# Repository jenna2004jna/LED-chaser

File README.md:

## Project Overview
Design an LED Chaser circuit (555 Timer + 4017 Decade Counter) and document the process for PCB fabrication using KiCad.

---

### 1. README (Project Introduction)

- **What is this?**
  An LED Chaser (aka LED Sequencer) using an NE555 Timer and CD4017 Decade Counter IC. This project demonstrates classic digital IC sequencing without microcontrollers.
- **Features:**
  - Chaser effect using 10 LEDs
  - Simple circuit, good for learning PCB design
  - Step-by-step development in KiCad
- **Repository Structure:**
  - `schematic/`   – KiCad schematic files
  - `pcb/`        – PCB layout files (KiCad)
  - `gerbers/`    – Generated manufacturing files
  - `docs/`       – Project documentation / images

---

### 2. Design Notes

- **Circuit Choice:**
  - 555 Timer (Astable mode) generates clock pulses
  - 4017 Decade Counter increments output, driving LEDs
- **Key Components:**
  - NE555 Timer IC
  - CD4017 Decade Counter IC
  - 10 LEDs (5mm, THT)
  - 10 Current limiting resistors (220Ω–330Ω)
  - Power: 5V or 9V
  - Decoupling capacitors (0.1µF at each IC's VCC/GND)
- **PCB Best Practices:**
  - Place ICs centrally
  - LED row for clear chaser effect
  - Power input near edge
  - Capacitors close to ICs
  - Use ground plane (GND zone) for noise immunity
  - Short 555-to-4017 clock trace
- **Fabrication:**
  - Run DRC in KiCad before generating Gerbers
  - Export Gerber and drill files for manufacturing (JLCPCB/PCBWay)

---

### 3. Bill of Materials (BOM)

| Qty | Reference           | Value         | Part Type   | Note                  |
|-----|---------------------|--------------|-------------|-----------------------|
| 1   | U1                  | NE555        | DIP-8       | Timer IC              |
| 1   | U2                  | CD4017       | DIP-16      | Decade Counter IC     |
| 10  | LED1–LED10          | 5mm          | THT         | Indicator LEDs        |
| 10  | R1–R10              | 220Ω–330Ω    | Axial       | LED current limiting  |
| 1   | R11                 | 10kΩ (ex)    | Axial       | 555 timing resistor   |
| 1   | C1                  | 10µF         | Radial      | 555 timing capacitor  |
| 2   | C2, C3              | 0.1µF        | Ceramic     | Decoupling capacitors |
| 1   | Conn1               | Power Input  | Header 2-pin| 5V or 9V supply       |

> Update ref/value as per your specific schematic.

---

### 4. Assembly & Testing Notes

- Solder components in order: resistors → IC sockets → LEDs → capacitors → power connector
- Double-check orientation of ICs and LEDs
- After assembly, power up and confirm LED chaser sequence
- If sequence fails, check clock trace length, decoupling cap placement, and solder joints

### 5. References & Further Reading

- [KiCad Official Documentation](https://docs.kicad.org/)
- [555 Timer & CD4017 datasheets](https://www.ti.com)
- [Example LED Chaser Circuits](https://www.electronics-tutorials.ws/sequential/seq_2.html)

---

**Maintainer:** jenna2004jna

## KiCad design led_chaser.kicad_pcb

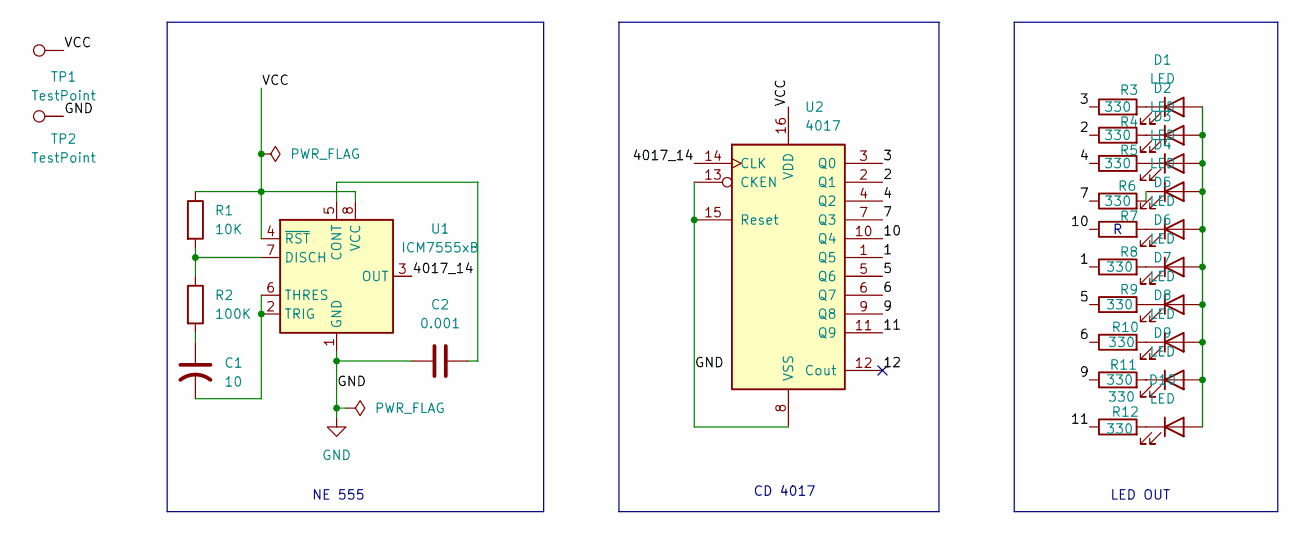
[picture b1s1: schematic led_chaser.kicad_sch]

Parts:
C1: 10; C_0805_2012Metric_Pad1.18x1.45mm_HandSolder
C2: 0.001; C_0805_2012Metric_Pad1.18x1.45mm_HandSolder
D1, D2, D3, D4, D5, D6, D7, D8, D9, D10: LED; LED_D5.0mm
R1: 10K; R_1206_3216Metric_Pad1.30x1.75mm_HandSolder
R2: 100K; R_1206_3216Metric_Pad1.30x1.75mm_HandSolder
R3, R4, R5, R6, R7, R8, R9, R10, R11, R12: 330; R_1206_3216Metric_Pad1.30x1.75mm_HandSolder
TP1, TP2: TestPoint; PinHeader_1x01_P2.54mm_Vertical
U1: ICM7555xB; SOIC-8_3.9x4.9mm_P1.27mm
U2: 4017; DIP-16_W7.62mm

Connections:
/1: R8.1, U2.1 (Q5)
/2: R4.1, U2.2 (Q1)
/3: R3.1, U2.3 (Q0)
/4: R5.1, U2.4 (Q2)
/5: R9.1, U2.5 (Q6)
/6: R10.1, U2.6 (Q7)
/7: R6.1, U2.7 (Q3)
/9: R11.1, U2.9 (Q8)
/10: R7.1, U2.10 (Q4)
/11: R12.1, U2.11 (Q9)
/12: U2.12 (Cout)
/4017_14: U1.3 (OUT), U2.14 (CLK)
/VCC: R1.1, TP1.1, U1.4 (~RST), U1.8 (VCC), U2.16 (VDD)
GND: C2.2, TP2.1, U1.1 (GND), U2.8 (VSS), U2.13 (CKEN), U2.15 (Reset)
unnamed: C1.1, R2.2
unnamed: D1.2 (A), D2.2 (A), D3.2 (A), D4.2 (A), D5.2 (A), D6.2 (A), D7.2 (A), D8.2 (A), D9.2 (A), D10.2 (A)
unnamed: D1.1 (K), R3.2
unnamed: D2.1 (K), R4.2
unnamed: D3.1 (K), R5.2
unnamed: D4.1 (K), R6.2
unnamed: D5.1 (K), R7.2
unnamed: D6.1 (K), R8.2
unnamed: D7.1 (K), R9.2
unnamed: D8.1 (K), R10.2
unnamed: D9.1 (K), R11.2
unnamed: D10.1 (K), R12.2
unnamed: C2.1, U1.5 (CONT)
unnamed: R1.2, R2.1, U1.7 (DISCH)
unnamed: C1.2, U1.2 (TRIG), U1.6 (THRES)

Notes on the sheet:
LED OUT
NE 555
CD 4017

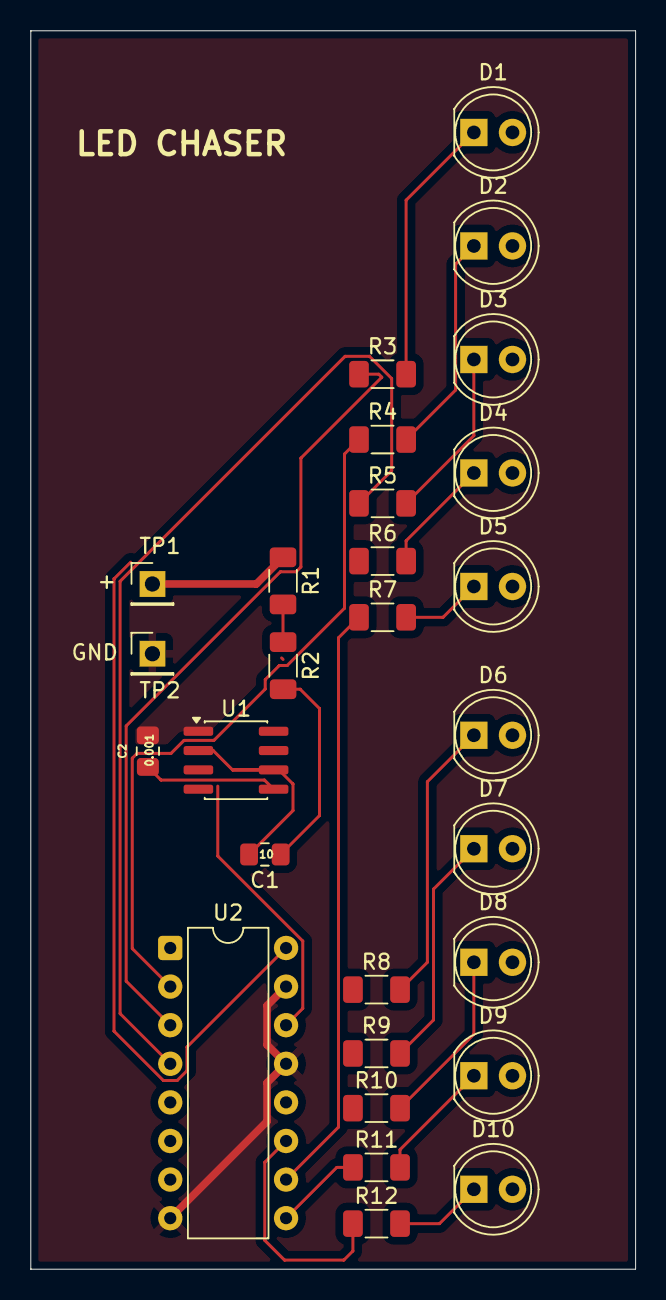
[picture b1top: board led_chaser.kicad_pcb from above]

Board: 2 copper layers, 39.8 x 81.5 mm, 28 parts (0 on the bottom side), 28 nets.

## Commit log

2026-03-03 Create README with project overview and details
    Add detailed project documentation for LED Chaser circuit.
